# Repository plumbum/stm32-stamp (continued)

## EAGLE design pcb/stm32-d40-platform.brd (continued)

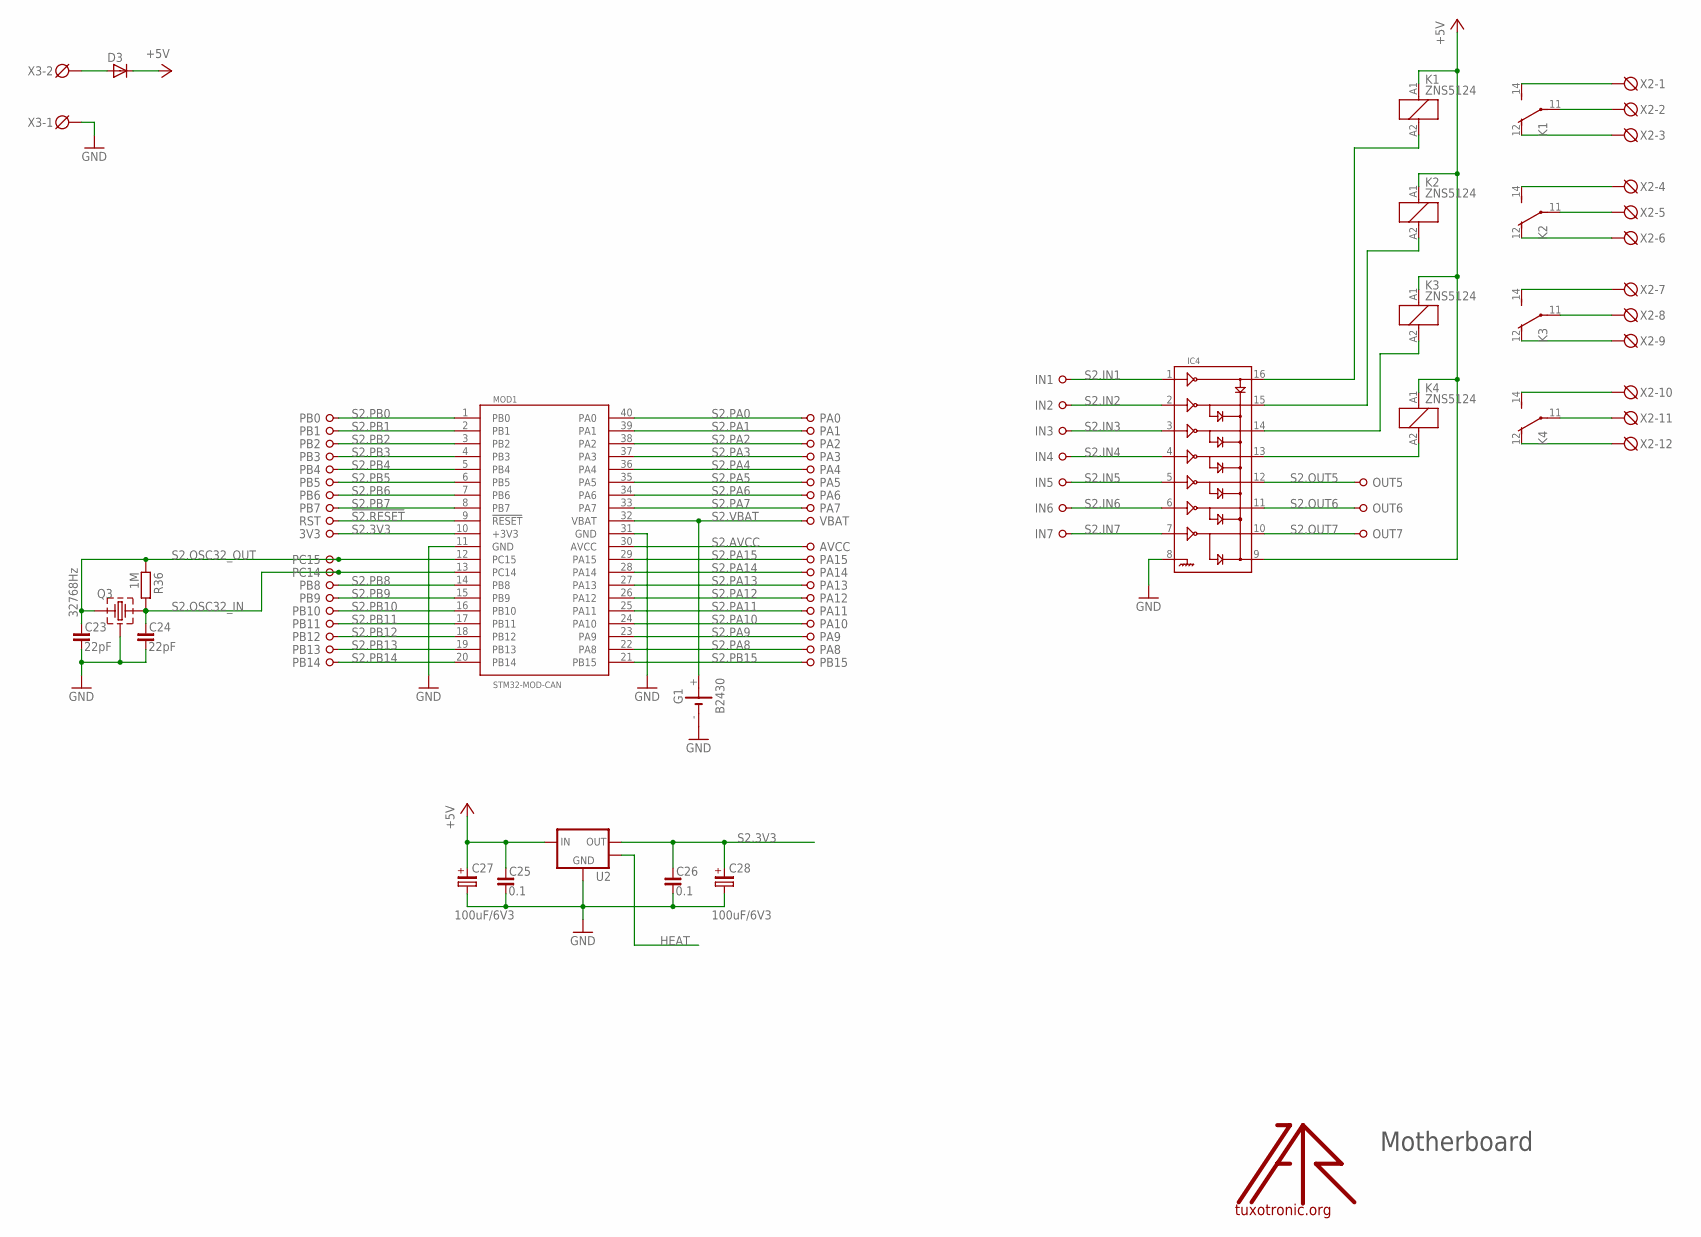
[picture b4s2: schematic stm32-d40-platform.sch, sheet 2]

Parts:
3V3: PIN-1X1_2.54; 1X01
AVCC: PIN-1X1_2.54; 1X01
C23, C24: 22pF; C0805
C25, C26: 0.1; C0805
C27, C28: 100uF/6V3; CE-035X080
D3: D-SMB; SMB
G1: B2430
IC4: ULN2003D; SO16
IN1, IN2, IN3, IN4, IN5, IN6, IN7: PIN-1X1_2.54; 1X01
K1, K2, K3, K4: ZNS5124; ZN5
MOD1: STM32-MOD-CAN; DIL40
OUT5, OUT6, OUT7: PIN-1X1_2.54; 1X01
PA0, PA1, PA2, PA3, PA4, PA5, PA6, PA7, PA8, PA9, PA10, PA11, PA12, PA13, PA14, PA15: PIN-1X1_2.54; 1X01
PB0, PB1, PB2, PB3, PB4, PB5, PB6, PB7, PB8, PB9, PB10, PB11, PB12, PB13, PB14, PB15: PIN-1X1_2.54; 1X01
PC14, PC15: PIN-1X1_2.54; 1X01
Q3: 32768Hz; TC38H-G
R36: 1M; R0805
RST: PIN-1X1_2.54; 1X01
U2: LM1117-3.3; SOT223
U$1: LOGO; TT_LOGO
VBAT: PIN-1X1_2.54; 1X01
X2: DG3XX-12-5.0; DG306-5.0-12P
X3: DG3XX-02-5.0; DG306-5.0-02P

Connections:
!S2.RESET: MOD1.9 (!RESET), RST.1
+5V: C25.1, C27.+, D3.C, IC4.9, K1.A1 (1), K2.A1 (1), K3.A1 (1), K4.A1 (1), U2.3 (IN); also elsewhere on the board
GND: C23.2, C24.2, C25.2, C26.2, C27.-, C28.-, G1.-, IC4.8, MOD1.11 (GND), MOD1.31 (GND), Q3.GND, U2.1 (GND), X3.1; also elsewhere on the board
HEAT: U2.4 (MASS)
unnamed: D3.A, X3.2
unnamed: K1.14 (S), X2.1
unnamed: K1.11, X2.2
unnamed: K1.12 (O), X2.3
unnamed: K2.14 (S), X2.4
unnamed: K2.11, X2.5
unnamed: K2.12 (O), X2.6
unnamed: K3.14 (S), X2.7
unnamed: K3.11, X2.8
unnamed: K3.12 (O), X2.9
unnamed: K4.14 (S), X2.10
unnamed: K4.11, X2.11
unnamed: K4.12 (O), X2.12
unnamed: IC4.13, K4.A2 (2)
unnamed: IC4.14, K3.A2 (2)
unnamed: IC4.15, K2.A2 (2)
unnamed: IC4.16, K1.A2 (2)
S2.3V3: 3V3.1, C26.1, C28.+, MOD1.10 (+3V3), U2.2 (OUT)
S2.AVCC: AVCC.1, MOD1.30 (AVCC)
S2.IN1: IC4.1, IN1.1
S2.IN2: IC4.2, IN2.1
S2.IN3: IC4.3, IN3.1
S2.IN4: IC4.4, IN4.1
S2.IN5: IC4.5, IN5.1
S2.IN6: IC4.6, IN6.1
S2.IN7: IC4.7, IN7.1
S2.OSC32_IN: C24.1, MOD1.13 (PC14), PC14.1, Q3.2, R36.2
S2.OSC32_OUT: C23.1, MOD1.12 (PC15), PC15.1, Q3.1, R36.1
S2.OUT5: IC4.12, OUT5.1
S2.OUT6: IC4.11, OUT6.1
S2.OUT7: IC4.10, OUT7.1
S2.PA0: MOD1.40 (PA0), PA0.1
S2.PA1: MOD1.39 (PA1), PA1.1
S2.PA2: MOD1.38 (PA2), PA2.1
S2.PA3: MOD1.37 (PA3), PA3.1
S2.PA4: MOD1.36 (PA4), PA4.1
S2.PA5: MOD1.35 (PA5), PA5.1
S2.PA6: MOD1.34 (PA6), PA6.1
S2.PA7: MOD1.33 (PA7), PA7.1
S2.PA8: MOD1.22 (PA8), PA8.1
S2.PA9: MOD1.23 (PA9), PA9.1
S2.PA10: MOD1.24 (PA10), PA10.1
S2.PA11: MOD1.25 (PA11), PA11.1
S2.PA12: MOD1.26 (PA12), PA12.1
S2.PA13: MOD1.27 (PA13), PA13.1
S2.PA14: MOD1.28 (PA14), PA14.1
S2.PA15: MOD1.29 (PA15), PA15.1
S2.PB0: MOD1.1 (PB0), PB0.1
S2.PB1: MOD1.2 (PB1), PB1.1
S2.PB2: MOD1.3 (PB2), PB2.1
S2.PB3: MOD1.4 (PB3), PB3.1
S2.PB4: MOD1.5 (PB4), PB4.1
S2.PB5: MOD1.6 (PB5), PB5.1
S2.PB6: MOD1.7 (PB6), PB6.1
S2.PB7: MOD1.8 (PB7), PB7.1
S2.PB8: MOD1.14 (PB8), PB8.1
S2.PB9: MOD1.15 (PB9), PB9.1
S2.PB10: MOD1.16 (PB10), PB10.1
S2.PB11: MOD1.17 (PB11), PB11.1
S2.PB12: MOD1.18 (PB12), PB12.1
S2.PB13: MOD1.19 (PB13), PB13.1
S2.PB14: MOD1.20 (PB14), PB14.1
S2.PB15: MOD1.21 (PB15), PB15.1
S2.VBAT: G1.+, MOD1.32 (VBAT), VBAT.1

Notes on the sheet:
Motherboard

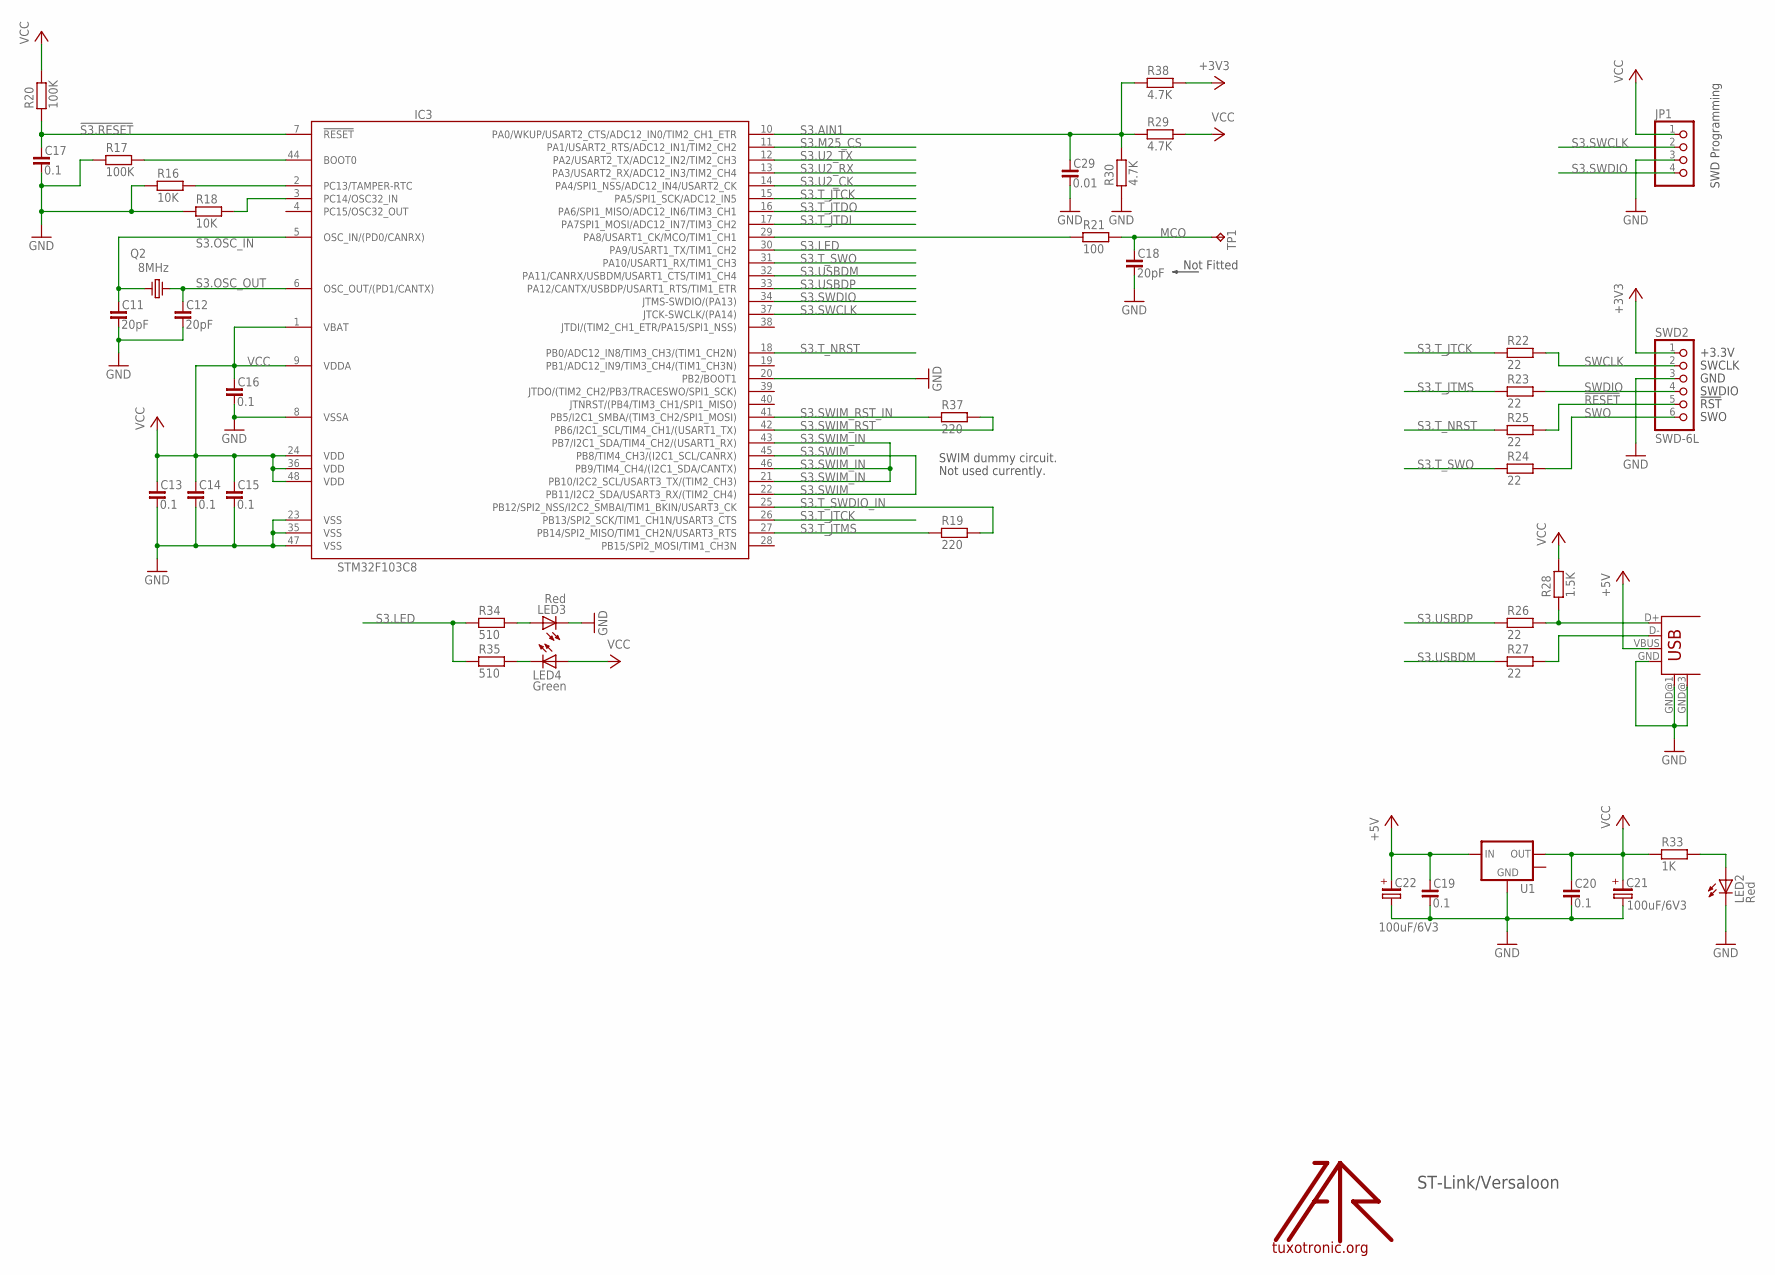
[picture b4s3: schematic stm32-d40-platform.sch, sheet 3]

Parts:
C11, C12, C18: 20pF; C0603
C13, C14, C15, C16, C17, C19, C20: 0.1; C0603
C21, C22: 100uF/6V3; SMC_C
C29: 0.01; C0603
IC3: STM32F103C8; LQFP48
JP1: PINHD-1X4_2.00; 1X04M
LED2, LED3: Red; CHIPLED_0603
LED4: Green; CHIPLED_0603
Q2: 8MHz; HC49/S
R16, R18: 10K; R0603
R17, R20: 100K; R0603
R19, R37: 220; R0603
R21: 100; R0603
R22, R23, R24, R25, R26, R27: 22; R0603
R28: 1.5K; R0603
R29, R30, R38: 4.7K; R0603
R33: 1K; R0603
R34, R35: 510; R0603
S3.LOGO: LOGO; TT_LOGO
SWD2: SWD-6L; SWD6PIN_L
TP1: TPB1,27; B1,27
U1: LM1117-3.3; SOT223
USB1: USB-MB-S2

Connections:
!RESET: R25.2, SWD2.5; also elsewhere on the board
!S3.RESET: C17.1, IC3.7 (!RESET), R20.1
+3V3: R38.2, SWD2.1; also elsewhere on the board
+5V: C19.1, C22.+, U1.3 (IN), USB1.VBUS; also elsewhere on the board
GND: C11.2, C12.2, C13.2, C14.2, C15.2, C16.2, C17.2, C18.2, C19.2, C20.2, C21.-, C22.-, C29.2, IC3.8 (VSSA), IC3.20 (PB2/BOOT1), IC3.23 (VSS), IC3.35 (VSS), IC3.47 (VSS), JP1.3, LED2.C, LED3.C, R16.1, R17.1, R18.1, R30.1, SWD2.3, U1.1 (GND), USB1.GND, USB1.GND@1 (GND), USB1.GND@3 (GND); also elsewhere on the board
MCO: C18.1, R21.2, TP1.PP
unnamed: IC3.44 (BOOT0), R17.2
unnamed: IC3.3 (PC14/OSC32_IN), R18.2
unnamed: IC3.2 (PC13/TAMPER-RTC), R16.2
unnamed: IC3.29 (PA8/USART1_CK/MCO/TIM1_CH1), R21.1
unnamed: R26.2, R28.1, USB1.D+
unnamed: R27.2, USB1.D-
unnamed: LED2.A, R33.2
unnamed: LED4.C, R35.2
unnamed: LED3.A, R34.2
S3.AIN1: C29.1, IC3.10 (PA0/WKUP/USART2_CTS/ADC12_IN0/TIM2_CH1_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), R29.1, R30.2, R38.1
S3.LED: IC3.30 (PA9/USART1_TX/TIM1_CH2), R34.1, R35.1
S3.M25_CS: IC3.11 (PA1/USART2_RTS/ADC12_IN1/TIM2_CH2)
S3.OSC_IN: C11.1, IC3.5 (OSC_IN/(PD0/CANRX)), Q2.1
S3.OSC_OUT: C12.1, IC3.6 (OSC_OUT/(PD1/CANTX)), Q2.2
S3.SWCLK: IC3.37 (JTCK-SWCLK/(PA14)), JP1.2
S3.SWDIO: IC3.34 (JTMS-SWDIO/(PA13)), JP1.4
S3.SWIM: IC3.22 (PB11/I2C2_SDA/USART3_RX/(TIM2_CH4)), IC3.45 (PB8/TIM4_CH3/(I2C1_SCL/CANRX))
S3.SWIM_IN: IC3.21 (PB10/I2C2_SCL/USART3_TX/(TIM2_CH3)), IC3.43 (PB7/I2C1_SDA/TIM4_CH2/(USART1_RX)), IC3.46 (PB9/TIM4_CH4/(I2C1_SDA/CANTX))
S3.SWIM_RST: IC3.42 (PB6/I2C1_SCL/TIM4_CH1/(USART1_TX)), R37.2
S3.SWIM_RST_IN: IC3.41 (PB5/I2C1_SMBA/(TIM3_CH2/SPI1_MOSI)), R37.1
S3.T_JTCK: IC3.15 (PA5/SPI1_SCK/ADC12_IN5), IC3.26 (PB13/SPI2_SCK/TIM1_CH1N/USART3_CTS), R22.1
S3.T_JTDI: IC3.17 (PA7SPI1_MOSI/ADC12_IN7/TIM3_CH2)
S3.T_JTDO: IC3.16 (PA6/SPI1_MISO/ADC12_IN6/TIM3_CH1)
S3.T_JTMS: IC3.27 (PB14/SPI2_MISO/TIM1_CH2N/USART3_RTS), R19.1, R23.1
S3.T_NRST: IC3.18 (PB0/ADC12_IN8/TIM3_CH3/(TIM1_CH2N)), R25.1
S3.T_SWDIO_IN: IC3.25 (PB12/SPI2_NSS/I2C2_SMBAI/TIM1_BKIN/USAR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), R19.2
S3.T_SWO: IC3.31 (PA10/USART1_RX/TIM1_CH3), R24.1
S3.U2_CK: IC3.14 (PA4/SPI1_NSS/ADC12_IN4/USART2_CK)
S3.U2_RX: IC3.13 (PA3/USART2_RX/ADC12_IN3/TIM2_CH4)
S3.U2_TX: IC3.12 (PA2/USART2_TX/ADC12_IN2/TIM2_CH3)
S3.USBDM: IC3.32 (PA11/CANRX/USBDM/USART1_CTS/TIM1_CH4), R27.1
S3.USBDP: IC3.33 (PA12/CANTX/USBDP/USART1_RTS/TIM1_ETR), R26.1
SWCLK: R22.2, SWD2.2; also elsewhere on the board
SWDIO: R23.2, SWD2.4; also elsewhere on the board
SWO: R24.2, SWD2.6; also elsewhere on the board
VCC: C13.1, C14.1, C15.1, C16.1, C20.1, C21.+, IC3.1 (VBAT), IC3.9 (VDDA), IC3.24 (VDD), IC3.36 (VDD), IC3.48 (VDD), JP1.1, LED4.A, R20.2, R28.2, R29.2, R33.1, U1.2 (OUT)

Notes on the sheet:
ST-Link/Versaloon
Not Fitted
SWD Programming
Not used currently.
SWIM dummy circuit.

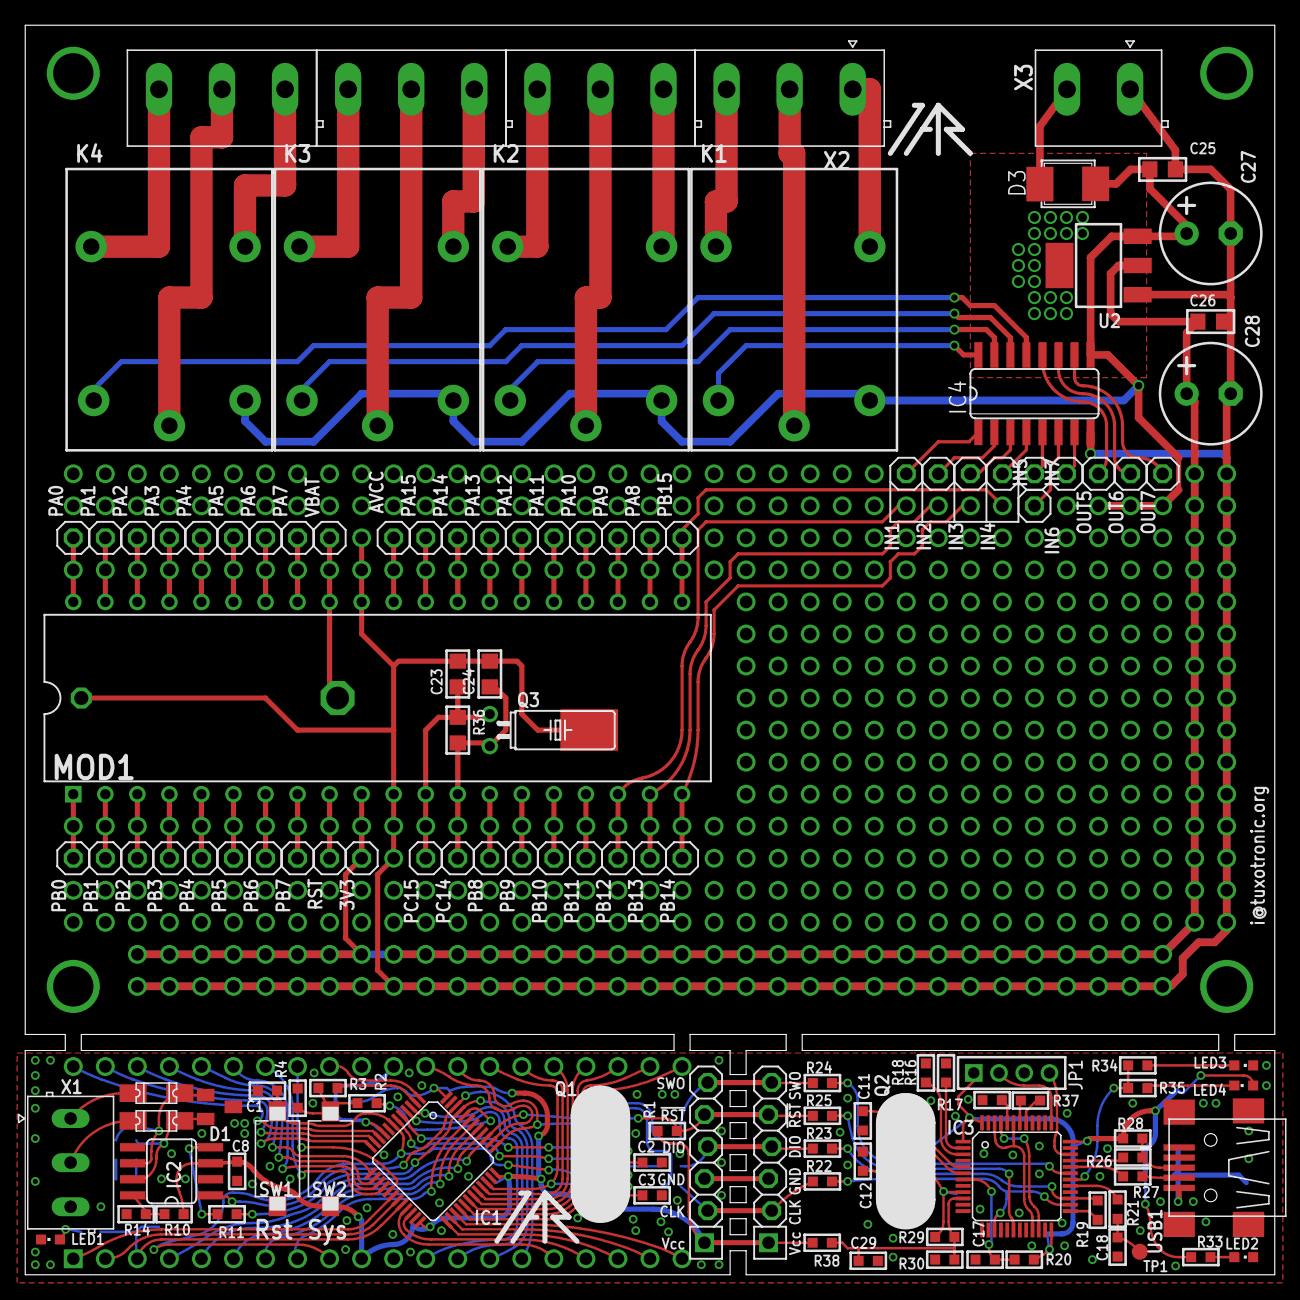
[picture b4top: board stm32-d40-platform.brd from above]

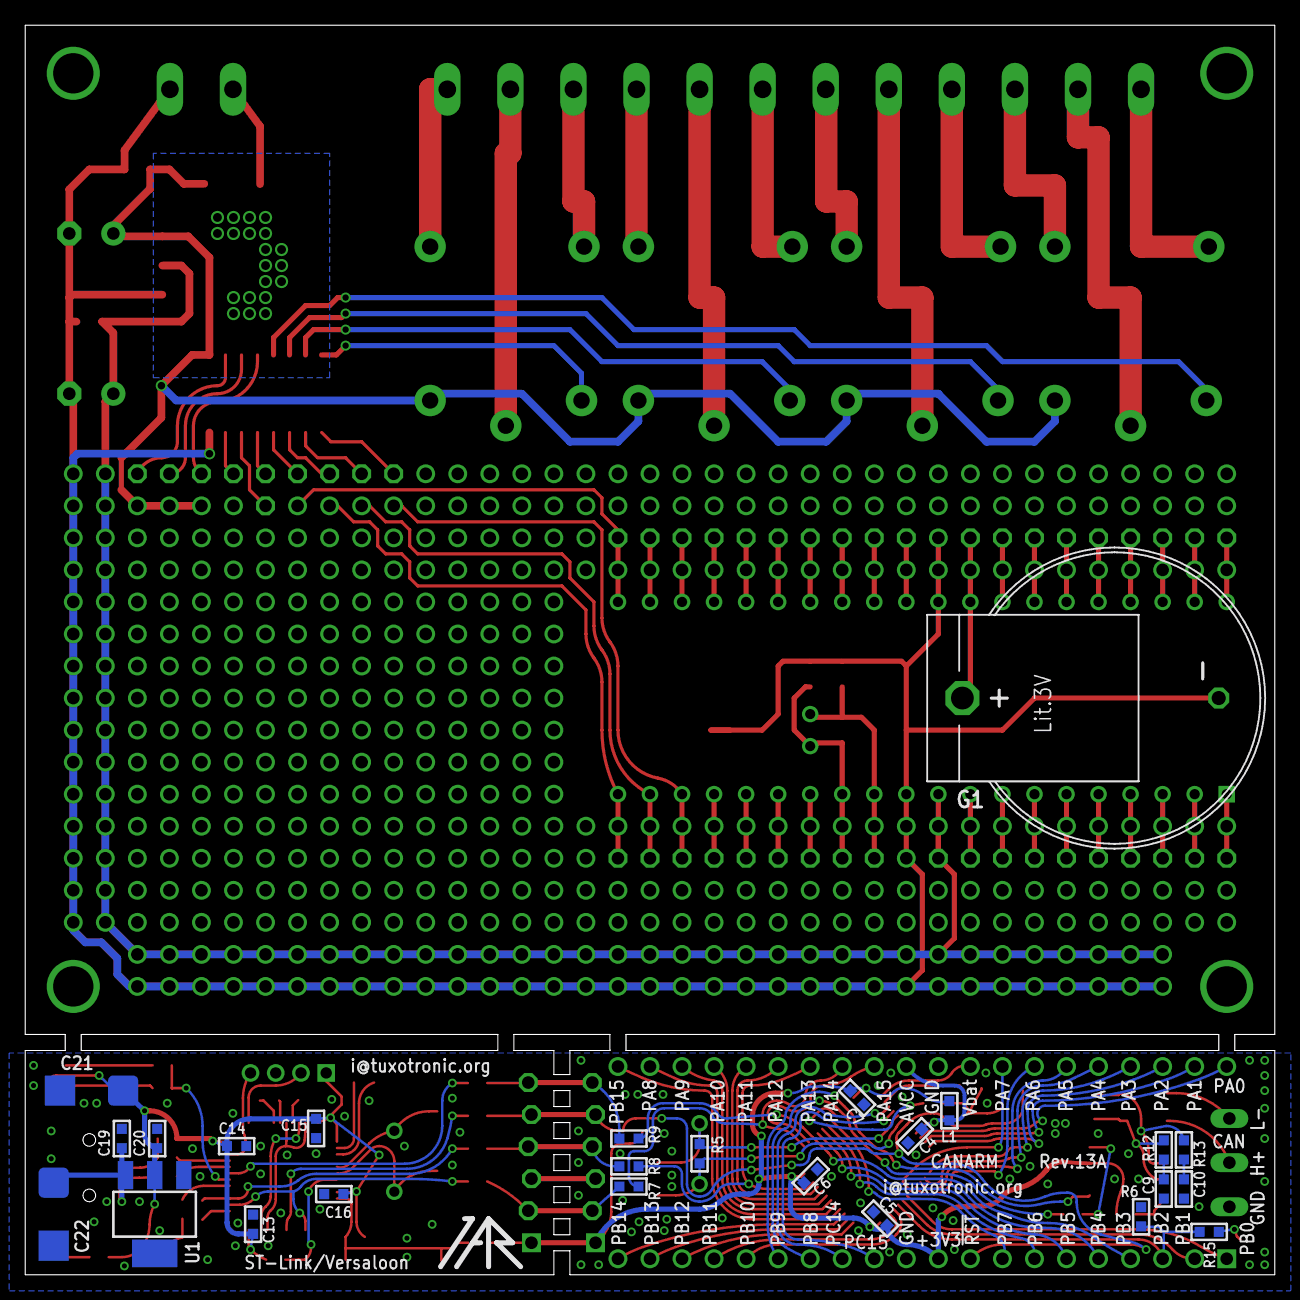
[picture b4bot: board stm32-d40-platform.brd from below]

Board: 2 copper layers, 99.1 x 99.1 mm, 151 parts (26 on the bottom side), 151 nets.

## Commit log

2011-09-15 some boards
2011-09-16 pcb in progress
2011-09-16 rename board, ignores
2012-01-13 stamp witch display on progress
2013-03-21 eagle 6.x
2013-04-02 route timers
2013-04-05 route in progress
2013-05-07 some pcb changes
2013-06-10 dip40-can
2013-06-11 dip40 in progress
2013-06-11 New DIP-40 board
2013-06-12 DIP40 CAN ready
2013-06-12 some wire fixes, add LED
2013-06-12 ST-Link / Versaloon tiny board
2013-06-12 motherboard in progress
2013-06-13 PCB ready
2013-06-13 Make gerbers
2013-07-25 stamp + lcd
2013-08-02 pcb...
2013-10-18 final route
2014-02-21 40 pin mesonine module done. Need check sch and pcb
2014-02-21 add description to schematic
2014-02-22 stm32-40 ready to production PCB. some changes in platform
2014-02-22 ST-link v2 SWD some fixes
2014-07-04 other boards
2014-07-04 some pcb fixes
2014-09-04 little button fix
2014-09-04 move old and partial boards to 'test'
2014-09-04 Rename board names
2015-04-08 Some fixes
2015-04-08 usb/microsd modification stamp
2015-04-08 stamp + proto
2015-04-08 esp-12 module fixes
2015-04-09 some fixes for gerber
2015-04-09 production ready, small fixes
2015-04-09 make gerber archive
2015-04-13 change link on silk layer
2015-06-01 fix jtag6 connector
2015-06-05 Add real board photos
